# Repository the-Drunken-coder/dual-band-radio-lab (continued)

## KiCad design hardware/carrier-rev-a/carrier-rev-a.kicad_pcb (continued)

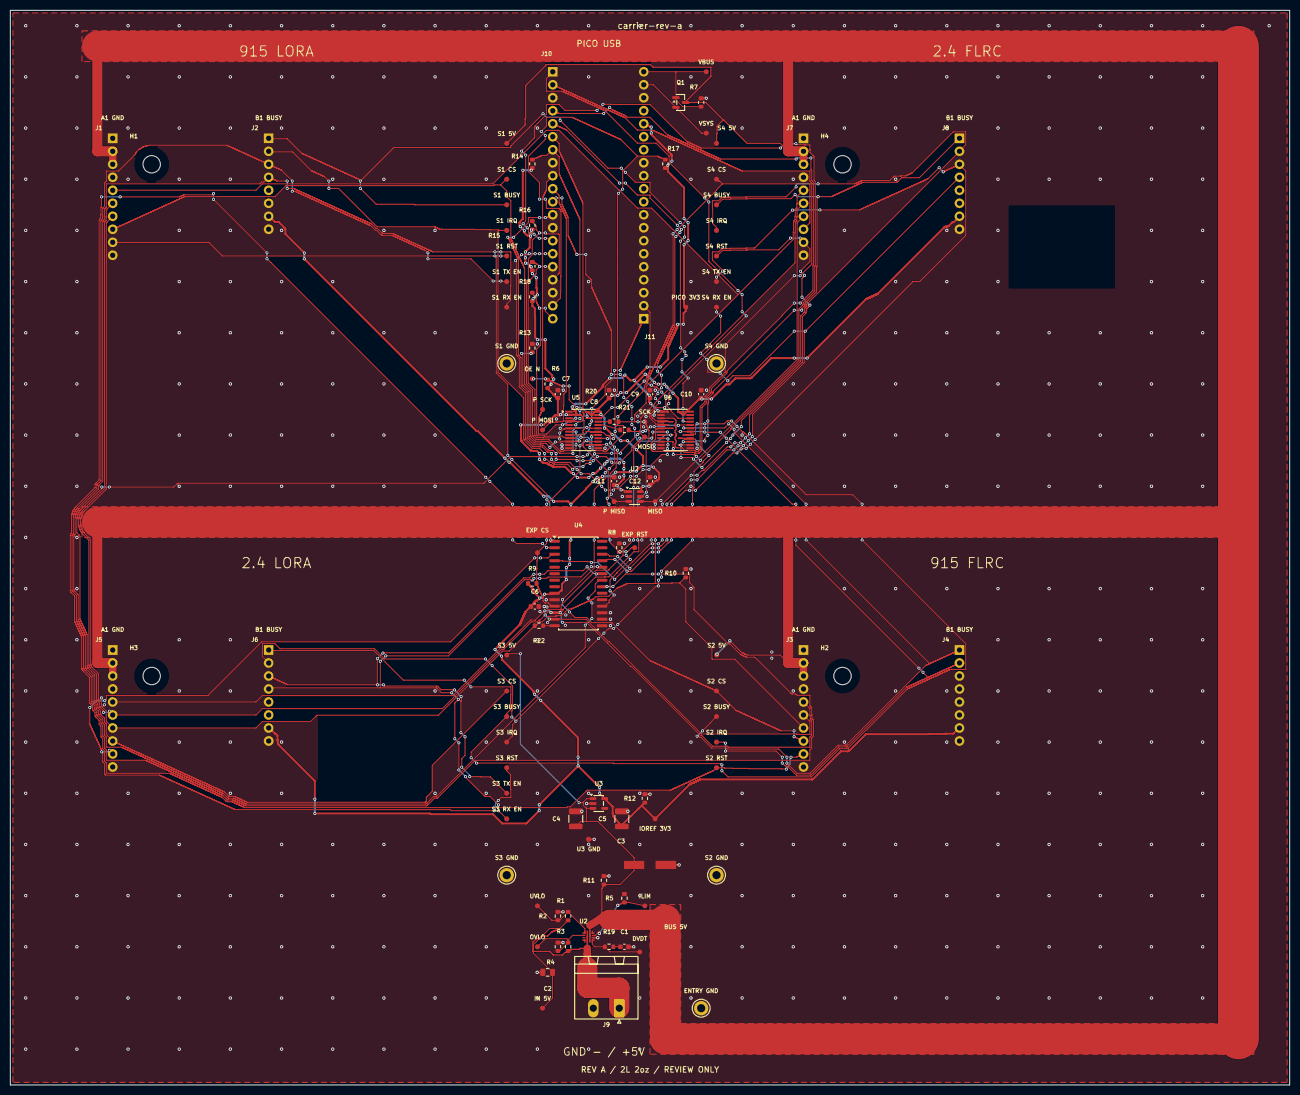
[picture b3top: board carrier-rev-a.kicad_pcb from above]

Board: 2 copper layers, 250.0 x 210.0 mm, 107 parts (0 on the bottom side), 60 nets.

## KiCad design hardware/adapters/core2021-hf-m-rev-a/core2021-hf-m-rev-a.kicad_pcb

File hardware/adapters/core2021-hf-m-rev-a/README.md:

# core2021-hf-m-rev-a

Editable Rev A schematic, routed PCB, selected BOM and schematic PDF. Native KiCad ERC and DRC pass with zero findings, including schematic parity. Two layers, 2 oz copper per side. Review only; no manufacturing release.

Open [core2021-hf-m-rev-a.kicad_pcb](core2021-hf-m-rev-a.kicad_pcb) in KiCad. The final native board is authoritative; do not overwrite it with the intermediate router session. See the hardware DESIGN_REVIEW.md, POWER_BUDGET.md and ASSEMBLY_NOTES.md for access, route lengths, power estimates and later physical acceptance.

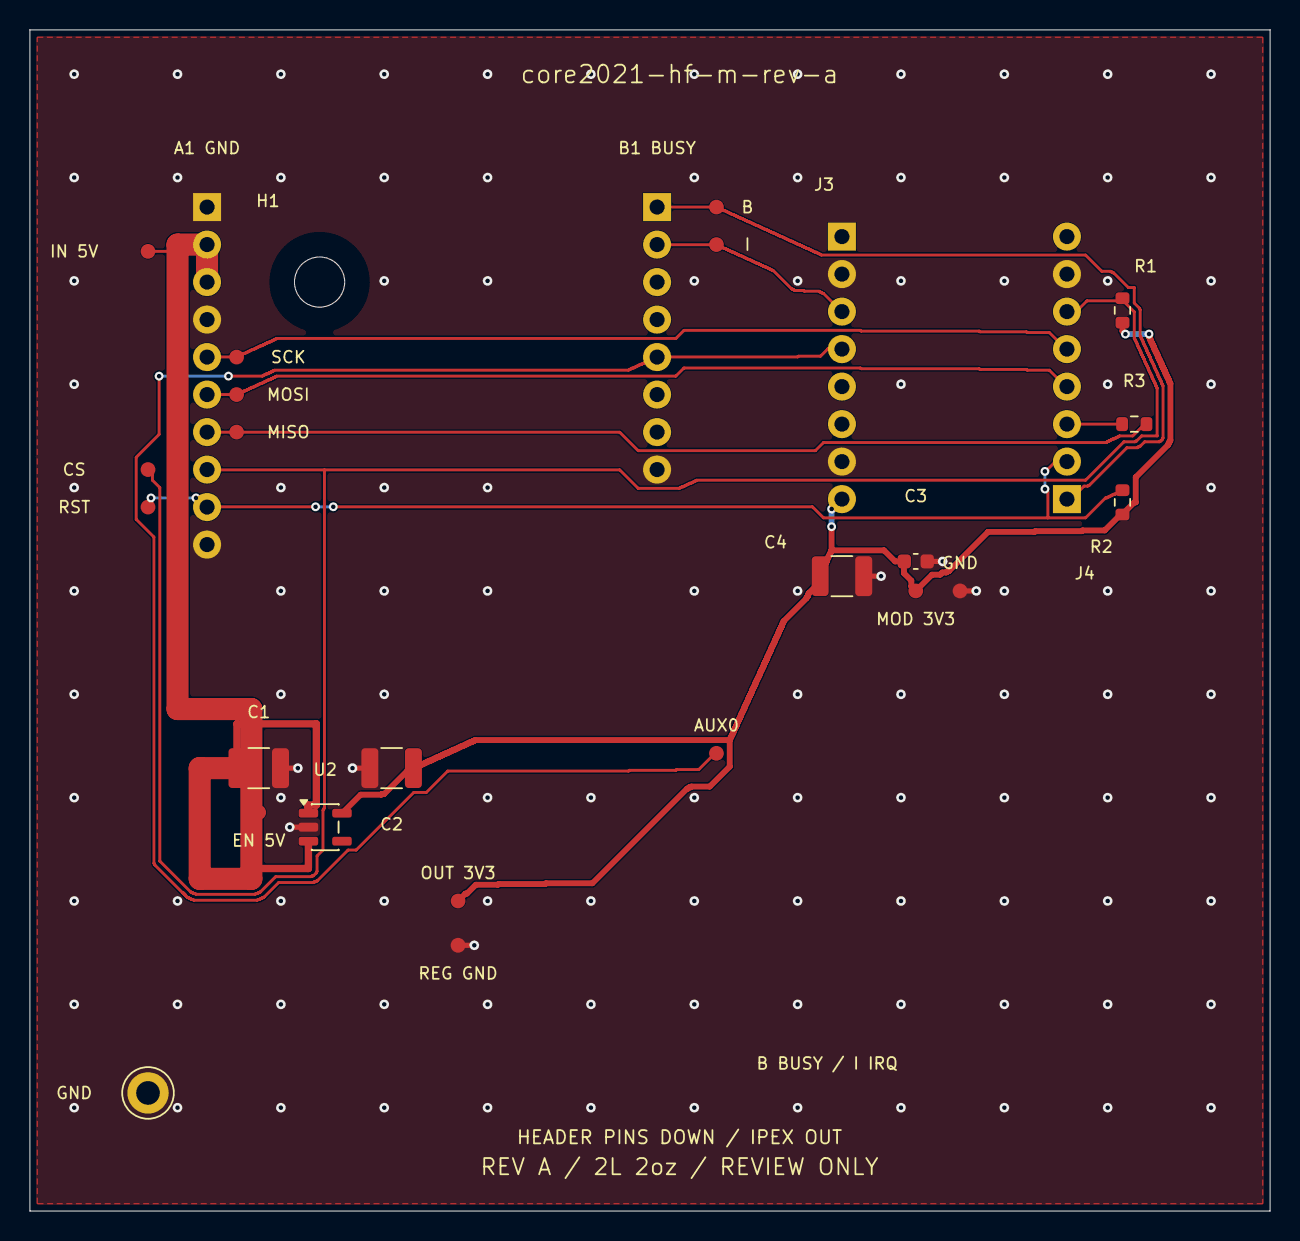
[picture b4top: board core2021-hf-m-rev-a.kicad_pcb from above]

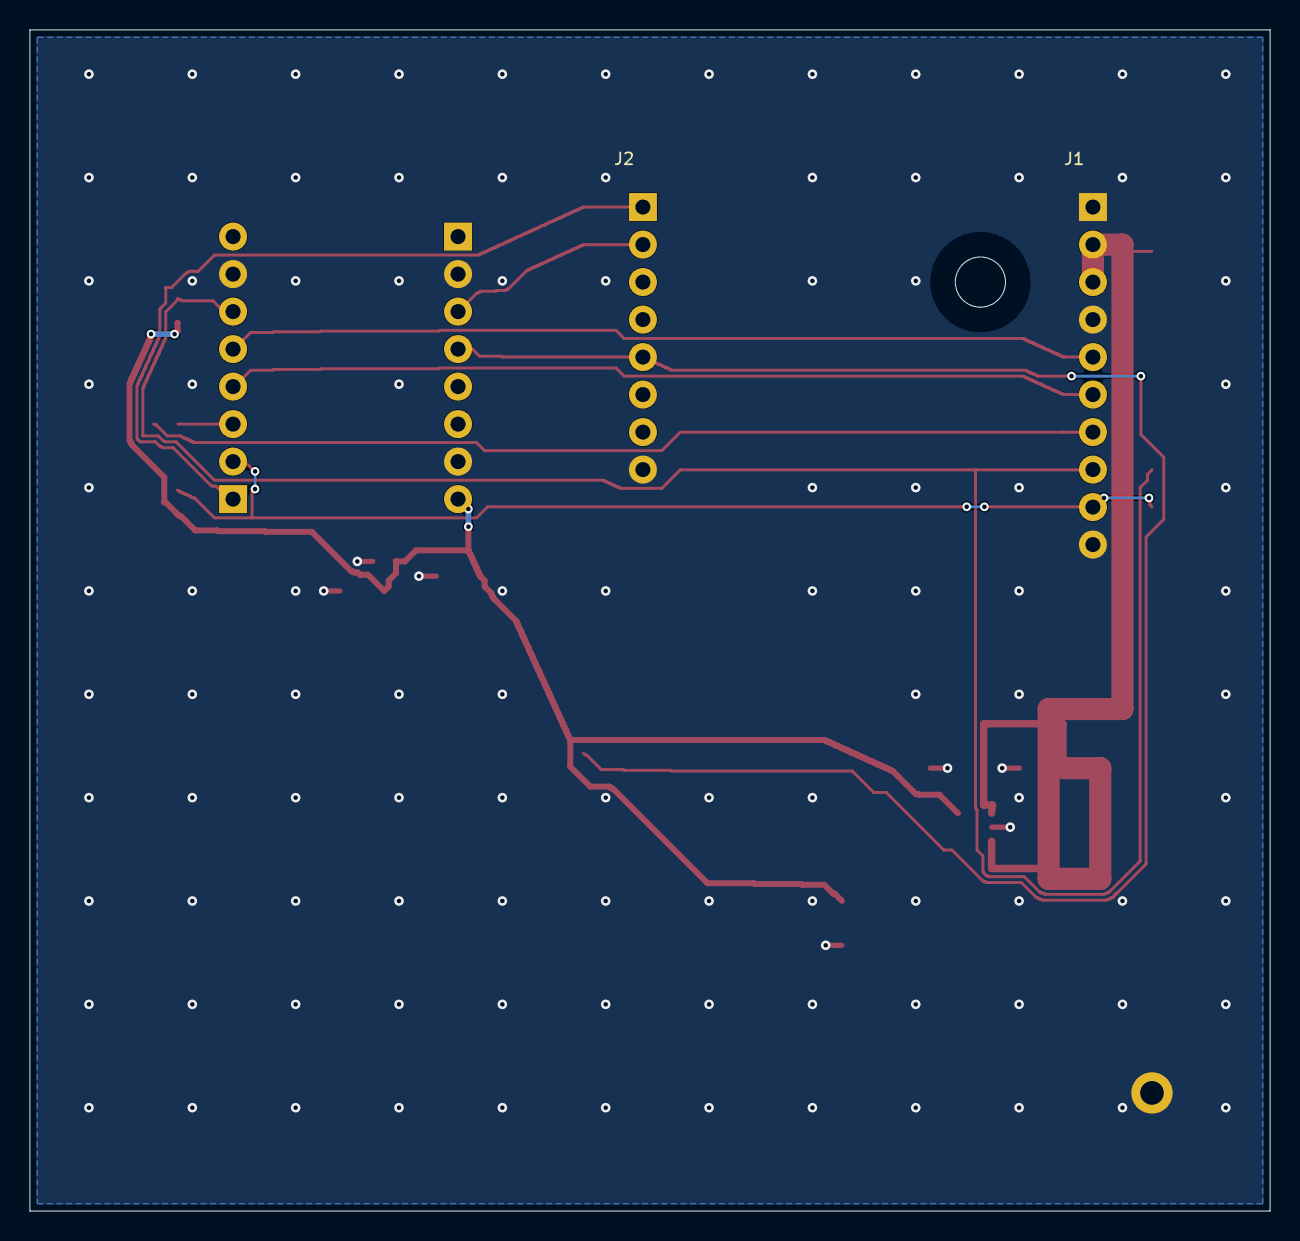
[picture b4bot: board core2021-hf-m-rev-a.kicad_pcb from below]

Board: 2 copper layers, 84.0 x 80.0 mm, 28 parts (2 on the bottom side), 12 nets.

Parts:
C1, C2, C4: 22uF; C_1210_3225Metric
C3: 100nF; C_0603_1608Metric
H1: M3 alignment hole; Alignment_M3_3.4mm
J1: TSW-110-07-G-S; TSW_1x10
J2: TSW-108-07-G-S; TSW_1x8
J3, J4: SSQ-108-01-G-S; SSQ_1x8
R1, R2: 10k; R_0603_1608Metric
R3: 22; R_0603_1608Metric
TP1: SPI_SCK; Probe_Pad_D1.0mm
TP2: SPI_MOSI; Probe_Pad_D1.0mm
TP3: SPI_MISO; Probe_Pad_D1.0mm
TP4: CS_N; Probe_Pad_D1.0mm
TP5: RESET_N; Probe_Pad_D1.0mm
TP6: BUSY; Probe_Pad_D1.0mm
TP7: IRQ; Probe_Pad_D1.0mm
TP8: IN_5V; Probe_Pad_D1.0mm
TP9: CLIP_GND; TestPoint_Keystone_5010-5014_Multipurpose
TP10: AUX0; Probe_Pad_D1.0mm
TP11: OUT_3V3; Probe_Pad_D1.0mm
TP12: REG_GND; Probe_Pad_D1.0mm
TP13: EN_5V; Probe_Pad_D1.0mm
TP14: MOD_3V3; Probe_Pad_D1.0mm
TP15: MOD_GND; Probe_Pad_D1.0mm
U2: AP2112K-3.3TRG1; SOT-23-5

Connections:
/AUX0: J2.5, J3.4, TP10.1
/BUSY: J2.1, J4.1, TP6.1
/CS_N: J1.8, J4.6, R1.2, TP4.1
/GND: C1.2, C2.2, C3.2, C4.2, J1.1, J1.4, J1.10, J2.8, J3.2, J3.7, J4.7, TP9.1, TP12.1, TP15.1, U2.2
/IRQ: J2.2, J3.3, TP7.1
/RADIO_3V3: C2.1, C3.1, C4.1, J3.8, R1.1, R2.1, TP11.1, TP14.1, U2.5
/RESET_N: J1.9, J4.2, R2.2, TP5.1
/SLOT_5V: C1.1, J1.2, J1.3, TP8.1, TP13.1, U2.1, U2.3
/SPI_MISO: J1.7, R3.2, TP3.1
/SPI_MISO_SRC: J4.3, R3.1
/SPI_MOSI: J1.6, J4.4, TP2.1
/SPI_SCK: J1.5, J4.5, TP1.1

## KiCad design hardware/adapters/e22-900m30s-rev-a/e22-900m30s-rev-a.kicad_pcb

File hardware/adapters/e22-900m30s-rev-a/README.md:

# e22-900m30s-rev-a

Editable Rev A schematic, routed PCB, selected BOM and schematic PDF. Native KiCad ERC and DRC pass with zero findings, including schematic parity. Two layers, 2 oz copper per side. Review only; no manufacturing release.

Open [e22-900m30s-rev-a.kicad_pcb](e22-900m30s-rev-a.kicad_pcb) in KiCad. The final native board is authoritative; do not overwrite it with the intermediate router session. See the hardware DESIGN_REVIEW.md, POWER_BUDGET.md and ASSEMBLY_NOTES.md for access, route lengths, power estimates and later physical acceptance.

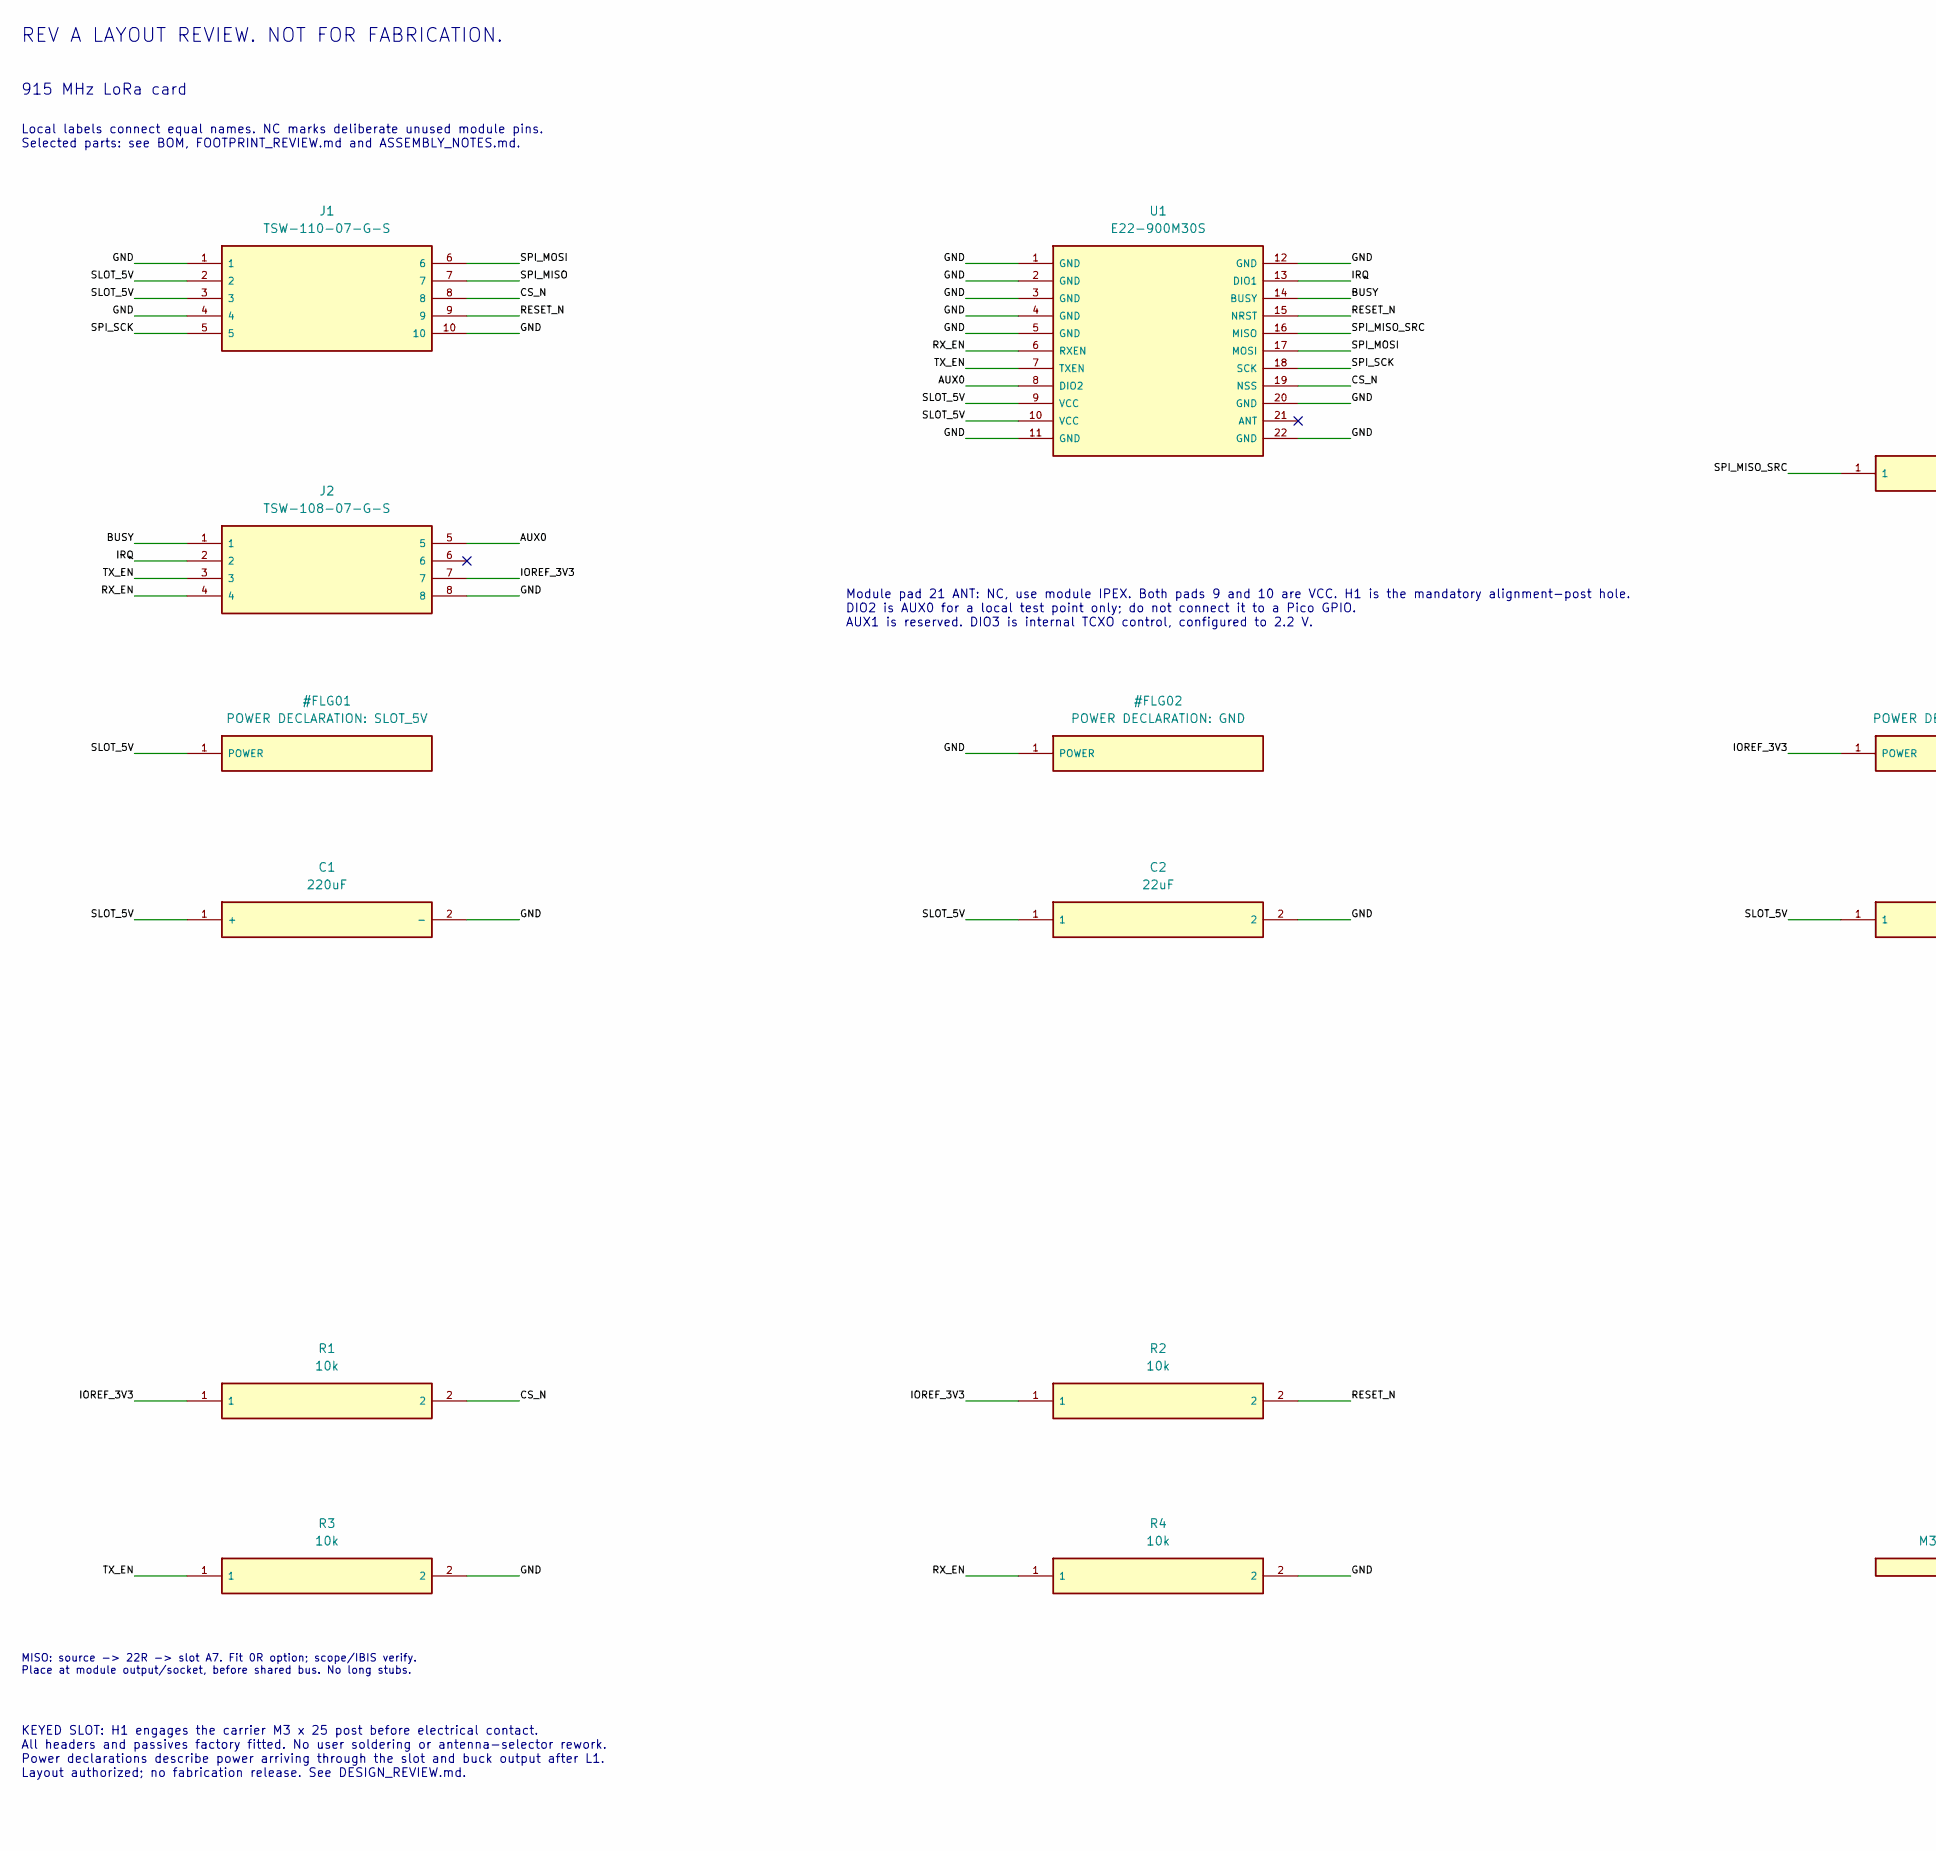
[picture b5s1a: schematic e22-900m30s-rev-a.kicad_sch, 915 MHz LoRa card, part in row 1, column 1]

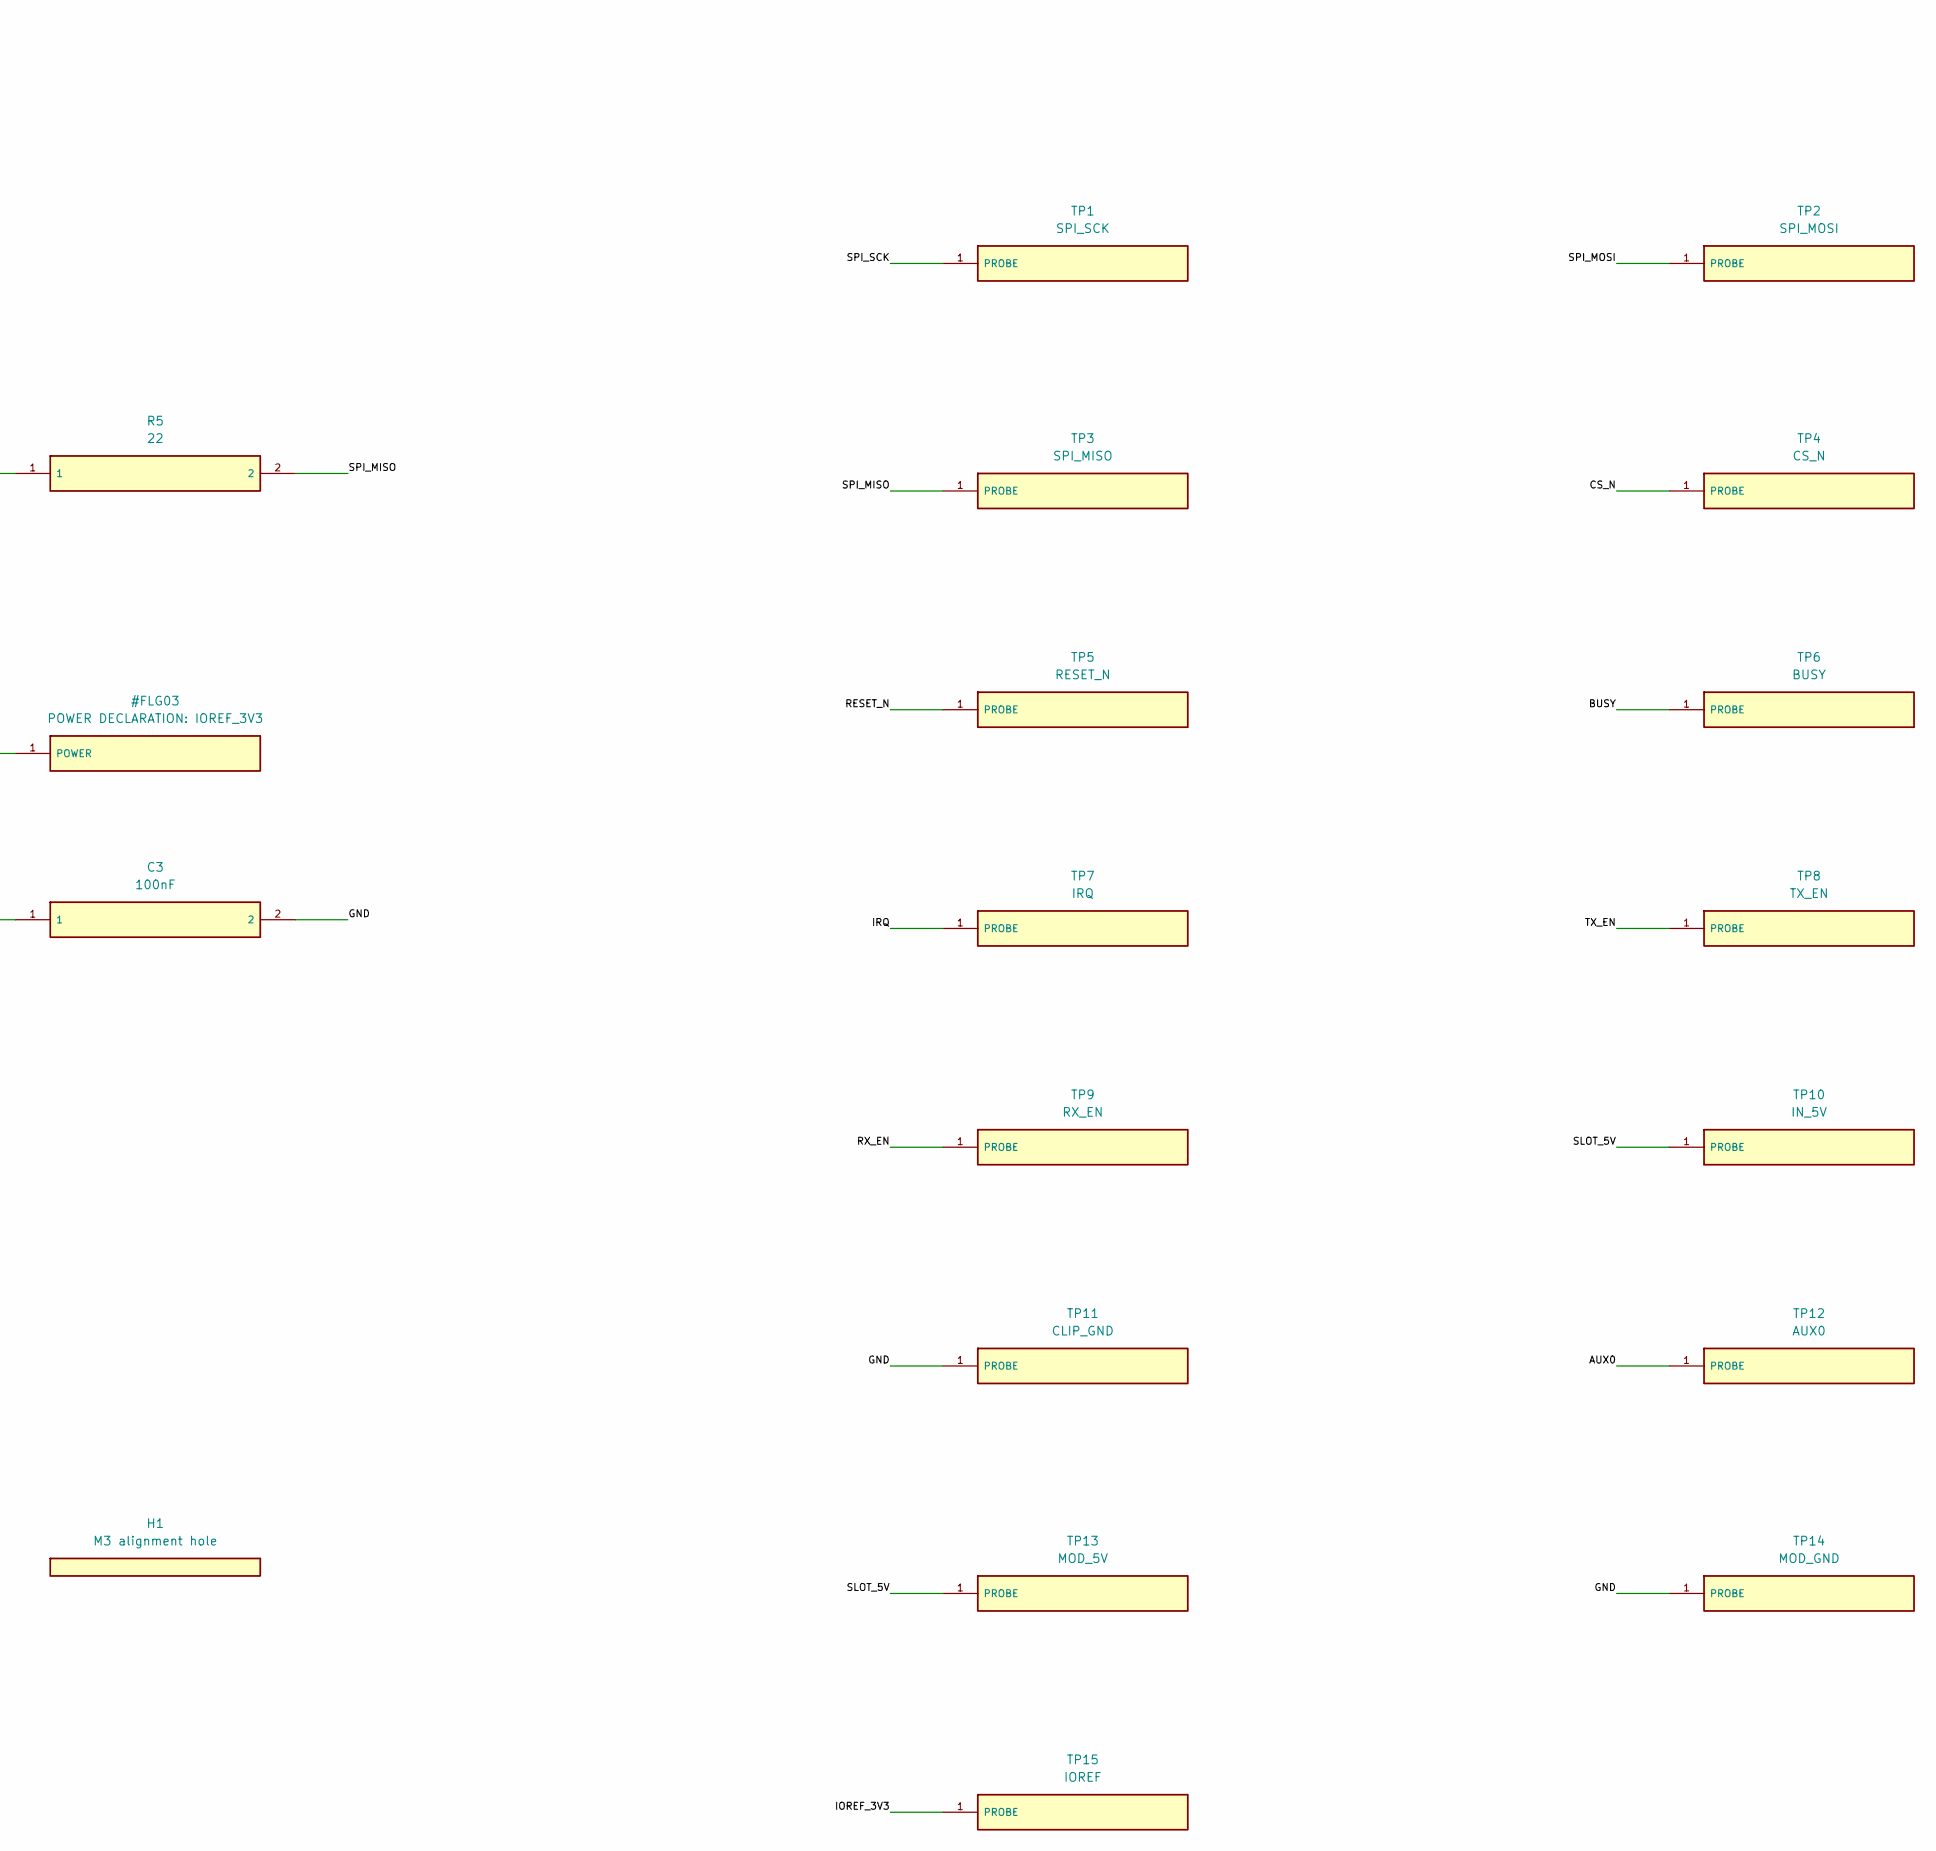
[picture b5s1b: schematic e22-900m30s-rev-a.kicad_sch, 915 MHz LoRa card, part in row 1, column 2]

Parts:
C1: 220uF; Panasonic_FK_E_8x6.2; MPN EEEFK1A221P
C2: 22uF; C_1210_3225Metric; MPN C3225X7R1E226M250AB
C3: 100nF; C_0603_1608Metric; MPN GRM188R71H104KA93D
H1: M3 alignment hole; Alignment_M3_3.4mm; MPN MECH-NPTH-3.4
J1: TSW-110-07-G-S; TSW_1x10; MPN TSW-110-07-G-S
J2: TSW-108-07-G-S; TSW_1x8; MPN TSW-108-07-G-S
R1, R2, R3, R4: 10k; R_0603_1608Metric; MPN RC0603FR-0710KL
R5: 22; R_0603_1608Metric; MPN RC0603FR-0722RL
TP1: SPI_SCK; Probe_Pad_D1.0mm; MPN PCB-PROBE-PAD
TP2: SPI_MOSI; Probe_Pad_D1.0mm; MPN PCB-PROBE-PAD
TP3: SPI_MISO; Probe_Pad_D1.0mm; MPN PCB-PROBE-PAD
TP4: CS_N; Probe_Pad_D1.0mm; MPN PCB-PROBE-PAD
TP5: RESET_N; Probe_Pad_D1.0mm; MPN PCB-PROBE-PAD
TP6: BUSY; Probe_Pad_D1.0mm; MPN PCB-PROBE-PAD
TP7: IRQ; Probe_Pad_D1.0mm; MPN PCB-PROBE-PAD
TP8: TX_EN; Probe_Pad_D1.0mm; MPN PCB-PROBE-PAD
TP9: RX_EN; Probe_Pad_D1.0mm; MPN PCB-PROBE-PAD
TP10: IN_5V; Probe_Pad_D1.0mm; MPN PCB-PROBE-PAD
TP11: CLIP_GND; TestPoint_Keystone_5010-5014_Multipurpose; MPN 5011
TP12: AUX0; Probe_Pad_D1.0mm; MPN PCB-PROBE-PAD
TP13: MOD_5V; Probe_Pad_D1.0mm; MPN PCB-PROBE-PAD
TP14: MOD_GND; Probe_Pad_D1.0mm; MPN PCB-PROBE-PAD
TP15: IOREF; Probe_Pad_D1.0mm; MPN PCB-PROBE-PAD
U1: E22-900M30S; E22_900M30S; MPN E22-900M30S

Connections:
/AUX0: J2.5, TP12.1, U1.8 (DIO2)
/BUSY: J2.1, TP6.1, U1.14 (BUSY)
/CS_N: J1.8, R1.2, TP4.1, U1.19 (NSS)
/GND: C1.2 (-), C2.2, C3.2, J1.1, J1.4, J1.10, J2.8, R3.2, R4.2, TP11.1, TP14.1, U1.1 (GND), U1.2 (GND), U1.3 (GND), U1.4 (GND), U1.5 (GND), U1.11 (GND), U1.12 (GND), U1.20 (GND), U1.22 (GND)
/IOREF_3V3: J2.7, R1.1, R2.1, TP15.1
/IRQ: J2.2, TP7.1, U1.13 (DIO1)
/RESET_N: J1.9, R2.2, TP5.1, U1.15 (NRST)
/RX_EN: J2.4, R4.1, TP9.1, U1.6 (RXEN)
/SLOT_5V: C1.1 (+), C2.1, C3.1, J1.2, J1.3, TP10.1, TP13.1, U1.9 (VCC), U1.10 (VCC)
/SPI_MISO: J1.7, R5.2, TP3.1
/SPI_MISO_SRC: R5.1, U1.16 (MISO)
/SPI_MOSI: J1.6, TP2.1, U1.17 (MOSI)
/SPI_SCK: J1.5, TP1.1, U1.18 (SCK)
/TX_EN: J2.3, R3.1, TP8.1, U1.7 (TXEN)

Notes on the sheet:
Module pad 21 ANT: NC, use module IPEX. Both pads 9 and 10 are VCC. H1 is the mandatory alignment-post hole. DIO2 is AUX0 for a local test point only; do not connect it to a Pico GPIO. AUX1 is reserved. DIO3 is internal TCXO control, configured to 2.2 V.
MISO: source -> 22R -> slot A7. Fit 0R option; scope/IBIS verify. Place at module output/socket, before shared bus. No long stubs.
KEYED SLOT: H1 engages the carrier M3 x 25 post before electrical contact. All headers and passives factory fitted. No user soldering or antenna-selector rework. Power declarations describe power arriving through the slot and buck output after L1. Layout authorized; no fabrication release. See DESI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
REV A LAYOUT REVIEW. NOT FOR FABRICATION.
915 MHz LoRa card
Local labels connect equal names. NC marks deliberate unused module pins. Selected parts: see BOM, FOOTPRINT_REVIEW.md and ASSEMBLY_NOTES.md.

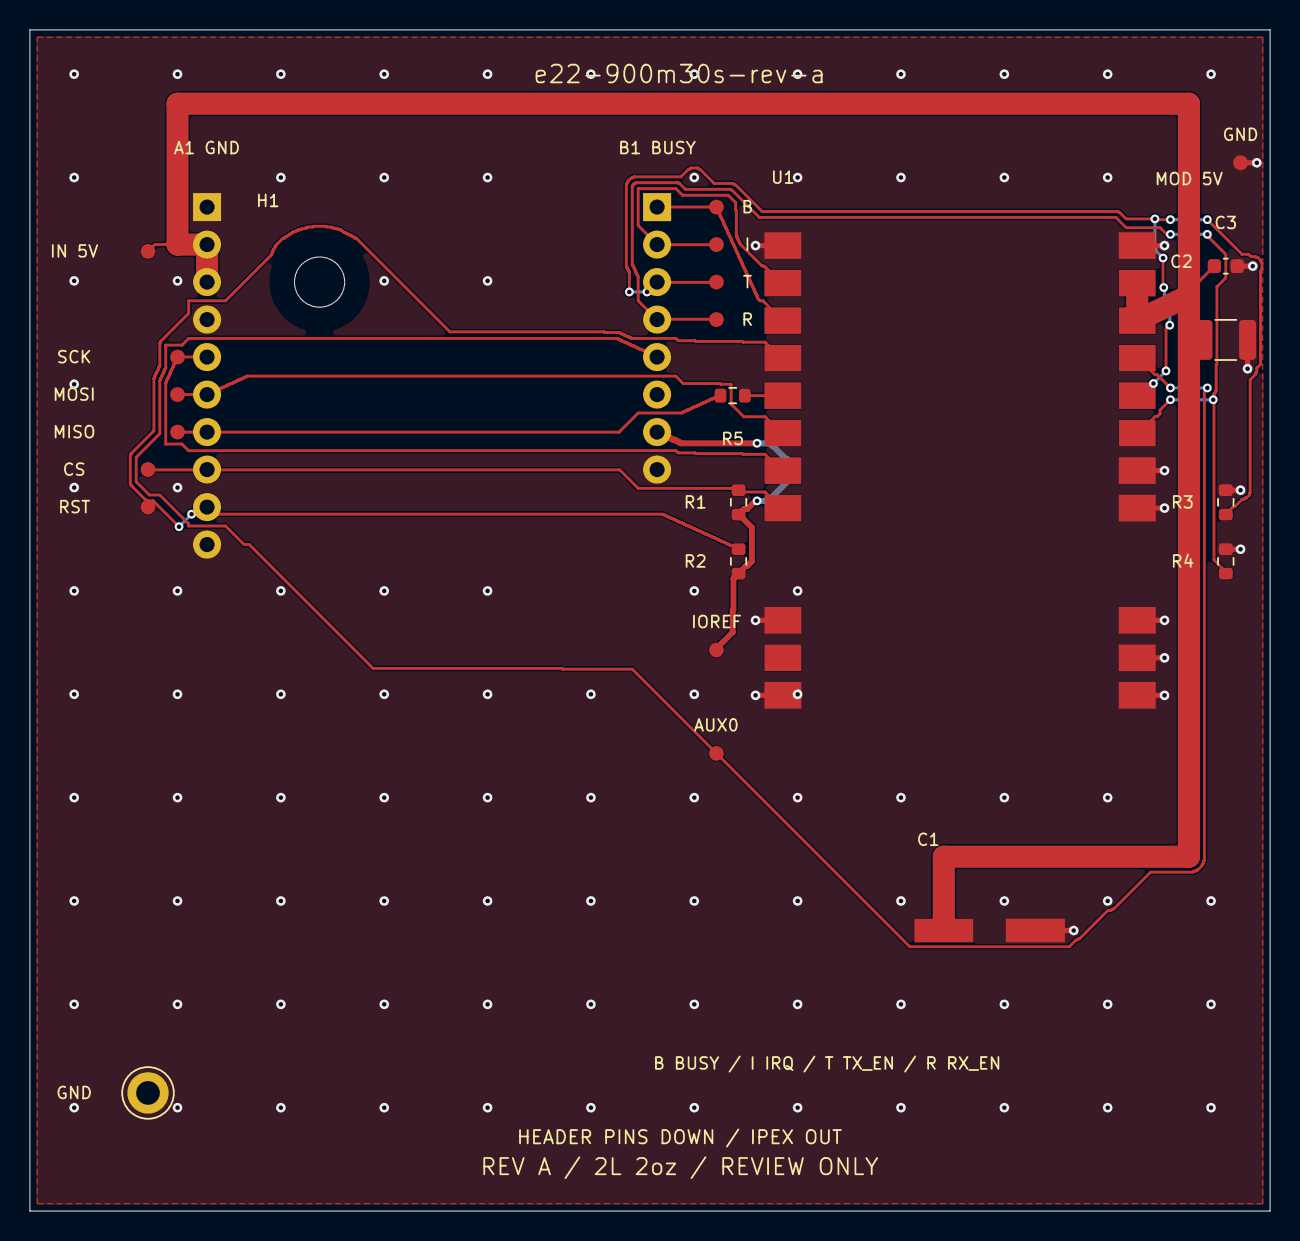
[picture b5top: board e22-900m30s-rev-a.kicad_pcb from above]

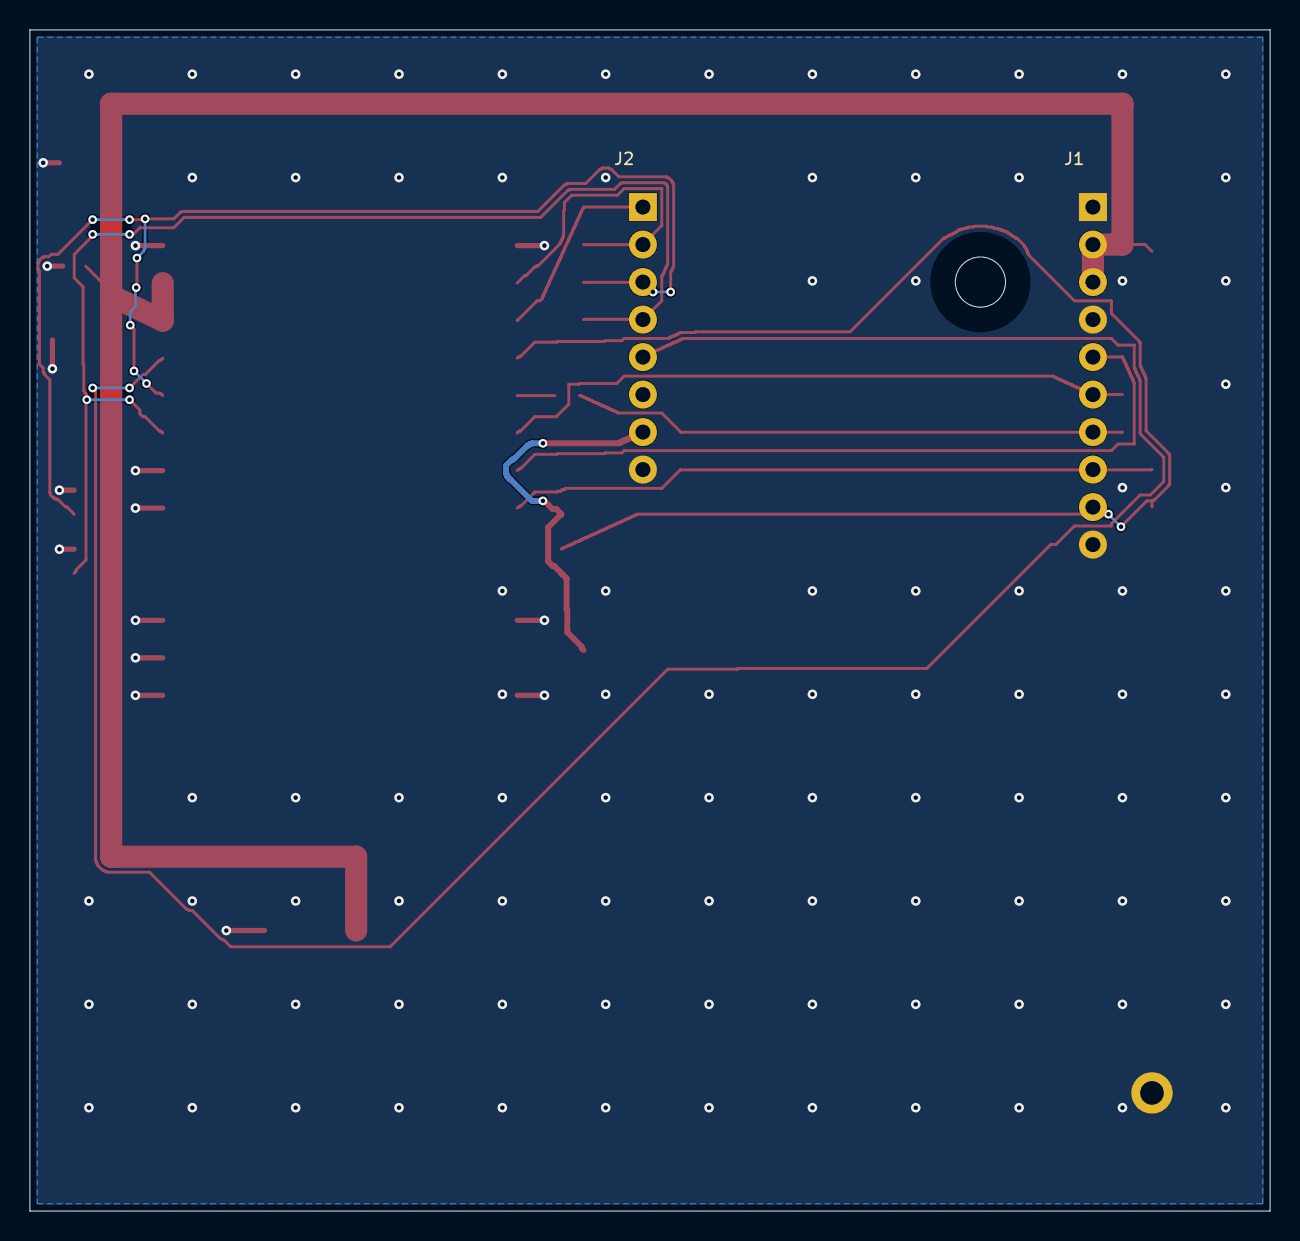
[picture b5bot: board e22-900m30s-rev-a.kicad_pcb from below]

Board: 2 copper layers, 84.0 x 80.0 mm, 27 parts (2 on the bottom side), 14 nets.

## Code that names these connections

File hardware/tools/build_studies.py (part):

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# Proposed interface. Its numbering is a design choice, not a vendor pin assignment.
SLOT_A = ["GND", "SLOT_5V", "SLOT_5V", "GND", "SPI_SCK", "SPI_MOSI", "SPI_MISO", "CS_N", "RESET_N", "GND"]
SLOT_B = ["BUSY", "IRQ", "TX_EN", "RX_EN", "AUX0", "AUX1", "IOREF_3V3", "GND"]
GPIO = {0: "S1_IRQ", 1: "S1_BUSY", 2: "S2_IRQ", 3: "S2_BUSY", 4: "SPI_MISO", 5: "S1_CS_N",
        6: "SPI_SCK", 7: "SPI_MOSI", 8: "S3_IRQ", 9: "S3_BUSY", 10: "S4_IRQ", 11: "S4_BUSY",
        12: "S2_CS_N", 13: "S3_CS_N", 14: "S4_CS_N", 15: "EXP_CS_N", 16: "EXP_RESET_N", 17: "IO_OE_N"}
EXPANDER = symbol("MCP23S17_SO", [(str(i), n, t) for i,n,t in
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        b.passive('C1','Capacitor','220uF',65,140,'SLOT_5V','GND','Local TX transient reservoir; 10 V polarized')
        b.passive('C2','Capacitor','22uF',185,140,'SLOT_5V','GND','Local supply decoupling')
        b.passive('C3','Capacitor','100nF',305,140,'SLOT_5V','GND','Local ceramic decoupling')
        b.text('Module pad 21 ANT: NC, use module IPEX. Both pads 9 and 10 are VCC. H1 is the mandatory alignment-post hole.\nDIO2 is AUX0 for a local test point only; do not connect it to a Pico GPIO.\nAUX1 is reserved. DIO3 is internal TCXO control, configured to 2.2 V.',140,100)
    elif kind == 'e28':
        nets={'1':'RADIO_3V3','2':'GND','3':'SPI_MISO_SRC','4':'SPI_MOSI','5':'SPI_SCK','6':'CS_N','7':'GND','8':'RX_EN','9':'TX_EN','10':'GND','11':'RESET_N','12':'BUSY','13':'IRQ','14':'AUX0','16':'GND'}
        b.part('U1',E28,'E28-2G4M27S',185,45,nets,'E28-2G4M27S','C411312',purpose='2.4 GHz lane; mandatory IPEX antenna variant',assembly='Factory: populate IPEX; selector link in manual 9.2 IPEX position, PCB-antenna branch open; no user rework',source='E28 manual section 3, PDF page 5')
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        b.part('U2',LDO,'AP2112K-3.3TRG1',305,45,{'1':'SLOT_5V','2':'GND','3':'SLOT_5V','5':'RADIO_3V3'},'AP2112K-3.3TRG1',purpose='Local 3.3 V supply',source='DS39724 Rev 2-2, pages 1-3')
        for ref,val,x,y,rail in [('C1','22uF',65,140,'SLOT_5V'),('C2','22uF',185,140,'RADIO_3V3'),('C3','100nF',305,140,'RADIO_3V3'),('C4','22uF',305,170,'RADIO_3V3')]:
            b.passive(ref,'Capacitor',val,x,y,rail,'GND','LDO/module ceramic decoupling')
        b.text('U1 represents the plug-in module, not a soldered module footprint.\nSocket contacts for module pins 1, 5, 6 and 16 are isolated.\nTX_EN/RX_EN slot contacts unused. No external RF switch added.\nJ3/J4: 15.24 mm row spacing; top/bottom numbering in FOOTPRINT_REVIEW.md.',140,100)
    source_location={'e22':'U1 MISO pad 16', 'e28':'U1 MISO pad 3', 'core':'J4 pin 3, nearest accessible Core U1 MISO pin 11'}[kind]
    b.series('R3' if kind=='core' else 'R5',305,75,'SPI_MISO_SRC','SPI_MISO',source_location)
    b.text('MISO: source -> 22R -> slot A7. Fit 0R option; scope/IBIS verify.\nPlace at module output/socket, before shared bus. No long stubs.',20.32,252,1.1)
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            ns[str(21-i)]=n+'_SRC' if ref=='U5' and n in ['SPI_SCK','SPI_MOSI'] else n
        b.part(ref,TRANS,'SN74LVC8T245PWR',x,250,ns,'SN74LVC8T245PWR',purpose='Dual-supply power-off isolation; fixed direction',source='SCES584D May 2026 sections 4,7.3.3,8.3')
    b.part('U7',TRANS1,'SN74LVC1T45DBVR',425,250,{'1':'PICO_3V3','2':'GND','3':'P_SPI_MISO','4':'SPI_MISO','5':'GND','6':'IOREF_3V3'},'SN74LVC1T45DBVR',purpose='MISO radio-to-Pico power-off isolation',source='SCES515N June 2024 sections 4 and 7')
    b.series('R20',185,305,'SPI_SCK_SRC','SPI_SCK','U5 B1 pin 21')
    b.series('R21',305,305,'SPI_MOSI_SRC','SPI_MOSI','U5 B2 pin 20')
    b.series('R22',665,135,'EXP_MISO_SRC','SPI_MISO','U4 SO pin 14')
    b.text('R20/R21: immediately after U5 SCK/MOSI outputs. R22: at U4 SO before shared MISO.\n22R initial; 0R population option. Verify by oscilloscope/IBIS. No long stubs.\nEach radio card has its own MISO source resistor before slot A7.',425,300)
    b.power_declaration('#FLG01','EXT_5V',425,190)
    b.power_declaration('#FLG02','GND',545,190)
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        b.passive(ref,sym,val,65+(i%7)*110,340+(i//7)*32,a,c,purpose)
    for i,n in enumerate(['S1_CS_N','S2_CS_N','S3_CS_N','S4_CS_N','EXP_CS_N']):
        b.passive('R'+str(14+i),'Resistor','10k',65+i*110,480,'PICO_3V3','P_'+n,'Pico-side deselect before enabling U5')
    b.passive('R19','Resistor','100',615,480,'DVDT','DVDT_C','TI recommended series damping for CdVdt above 10 nF including tolerance')
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    for i in range(4):
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
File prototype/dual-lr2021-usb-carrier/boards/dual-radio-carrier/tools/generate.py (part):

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    pin_map={}
    for label,upper,lower,origin,sx in [('A','J3','J4',[45,20],187.96),('B','J5','J6',[75,48],294.64)]:
        function_net={'3V3':'+3V3_RADIO','GND':'GND','DIO11':f'RADIO_{label}_DIO11',
                      'BUSY':f'RADIO_{label}_BUSY','RESET':f'RADIO_{label}_RESET_N',
                      'NSS':f'RADIO_{label}_CS_N','MISO':'SPI_MISO','MOSI':'SPI_MOSI','SCK':'SPI_SCK'}
        for ref,pin_order,offset,sy in [(upper,list(range(8,0,-1)),0,43.18),(lower,list(range(9,17)),15.24,86.36)]:
            pins=[]
            for number in pin_order:
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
